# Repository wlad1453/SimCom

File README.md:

# SimCom
This project realizes an ultrasonic distance measurement and determines a presence time of a truck in the measurement field. These data are send to the server via GPRS/HTTP technology. On the server side this data are analized and an intermediate data file (sim800truck_data.txt) as well as an DB entry are created or updated.
The visualization of the actual data is done via WEB interface (sim800data.php). 
With the help of a JS scripts and AJAX method the data file sim800truck_data.txt and the last db entry is read every 500 mS and the actual data are
presented via WEB-inteface.

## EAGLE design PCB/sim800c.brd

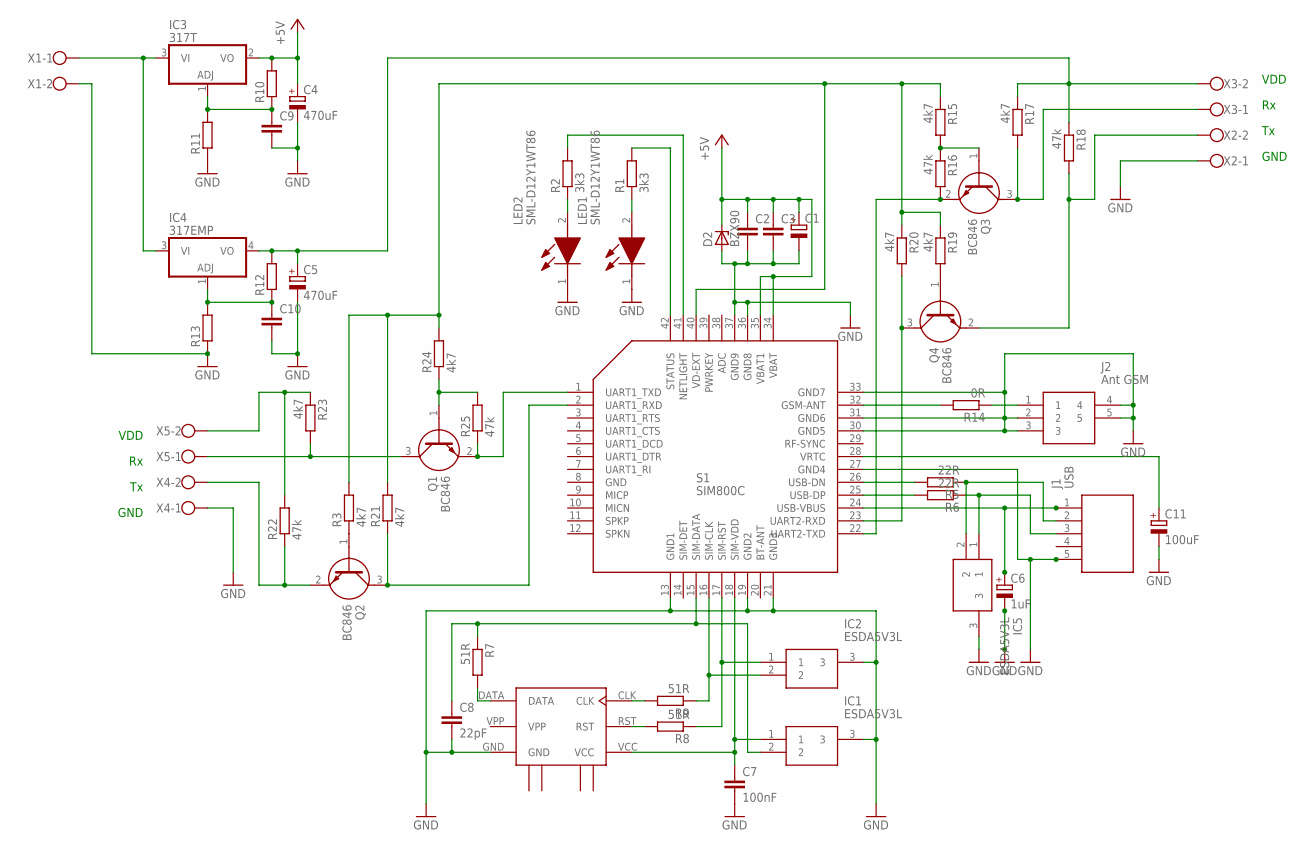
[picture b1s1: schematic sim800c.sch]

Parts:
C1: CPOL-EU140CLH-0810; 140CLH-0810
C2, C3, C9, C10: C-EUC0603; C0603
C4, C5: 470uF; 140CLH-1010
C6: 1uF; 153CLV-0405
C7: 100nF; C0805
C8: 22pF; C0805
C11: 100uF; 140CLH-0810
D2: BZX90; DO34Z7
IC1: ESDA5V3L; SOT105P242X150-3N
IC2, IC5: ESDA5V3L; SOT105P242X150-3N; MANUFACTURER_PART_NUMBER ESDA5V3L; MOUSER_PART_NUMBER 511-ESDA5V3L
IC3: 317T; TO220H
IC4: 317EMP; SOT223
J1: USB; ZX62R-B-5P(30)
J2: Ant GSM; 10533541
LED1, LED2: SML-D12Y1WT86; LEDC1608X55N
Q1, Q2: BC846; SOT95P230X110-3N
Q3, Q4: BC846; SOT95P230X110-3N; MANUFACTURER_PART_NUMBER BC846B,215; MOUSER_PART_NUMBER 771-BC846B-T/R
R1, R2: 3k3; M0805
R3, R15, R17, R19, R20, R21, R23, R24: 4k7; M1206
R5, R6: 22R; M1206
R7, R8, R9: 51R; M1206
R10, R11, R12, R13: R-EU_M1206; M1206
R14: 0R; M1206
R16, R18, R22, R25: 47k; M1206
S1: SIM800C
U$1: SCU-W0822XR-06
X1, X2, X4: W237-102
X3, X5: W237-102; MPN 237-102

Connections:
+5V: C1.+, C2.1, C3.1, C4.+, D2.C, IC3.2 (VO), R10.2, S1.34 (VBAT), S1.35 (VBAT1)
GND: C1.-, C2.2, C3.2, C4.-, C5.-, C6.-, C7.2, C8.2, C9.2, C10.2, C11.-, D2.A, IC1.3, IC2.3, IC5.3, J1.5, J2.2, J2.3, J2.4, J2.5, LED1.1 (K), LED2.1 (K), R11.1, R13.1, S1.8 (GND), S1.13 (GND1), S1.19 (GND2), S1.21 (GND3), S1.27 (GND4), S1.30 (GND5), S1.31 (GND6), S1.33 (GND7), S1.36 (GND8), S1.37 (GND9), U$1.GND, X1.2, X2.1, X4.1
GND1: U$1.GND_1 (GND1)
GND2: U$1.GND_2 (GND2)
GND3: U$1.GND_3 (GND3)
GND4: U$1.GND_4 (GND4)
unnamed: Q3.2 (E), R16.2, S1.22 (UART2-TXD)
unnamed: R6.2, S1.25 (USB-DP)
unnamed: C6.+, J1.1, S1.24 (USB-VBUS)
unnamed: IC5.2, J1.2, R5.1
unnamed: R14.2, S1.32 (GSM-ANT)
unnamed: LED1.2 (A), R1.1
unnamed: LED2.2 (A), R2.1
unnamed: Q1.3 (C), R23.2, X5.1
unnamed: Q1.1 (B), R24.1, R25.2
unnamed: IC5.1, J1.3, R6.1
unnamed: Q2.3 (C), R21.1, S1.2 (UART1_RXD)
unnamed: R7.2, U$1.DATA
unnamed: IC2.2, R9.1, S1.16 (SIM-CLK)
unnamed: IC2.1, R8.1, S1.17 (SIM-RST)
unnamed: IC3.3 (VI), IC4.3 (VI), X1.1
unnamed: C7.1, IC1.1, S1.18 (SIM-VDD), U$1.VCC
unnamed: C8.1, IC1.2, R7.1, S1.15 (SIM-DATA)
unnamed: C9.1, IC3.1 (ADJ), R10.1, R11.2
unnamed: R9.2, U$1.CLK
unnamed: J2.1, R14.1
unnamed: R8.2, U$1.RST
unnamed: R2.2, S1.41 (NETLIGHT)
unnamed: R1.2, S1.42 (STATUS)
unnamed: C10.1, IC4.1 (ADJ), R12.1, R13.2
unnamed: C11.+, S1.28 (VRTC)
unnamed: Q3.1 (B), R15.2, R16.1
unnamed: C5.+, IC4.4 (VO), R12.2, R17.1, R18.1, X3.2
unnamed: R5.2, S1.26 (USB-DN)
unnamed: R3.2, R15.1, R19.1, R20.1, R21.2, R24.2, S1.40 (VD-EXT)
unnamed: Q2.2 (E), R22.1, X4.2
unnamed: Q3.3 (C), R17.2, X3.1
unnamed: Q2.1 (B), R3.1
unnamed: Q4.1 (B), R19.2
unnamed: Q4.3 (C), R20.2, S1.23 (UART2-RXD)
unnamed: Q4.2 (E), R18.2, X2.2
unnamed: R22.2, R23.1, X5.2
S$3: Q1.2 (E), R25.1, S1.1 (UART1_TXD)
VPP: U$1.VPP

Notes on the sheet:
VDD
GND

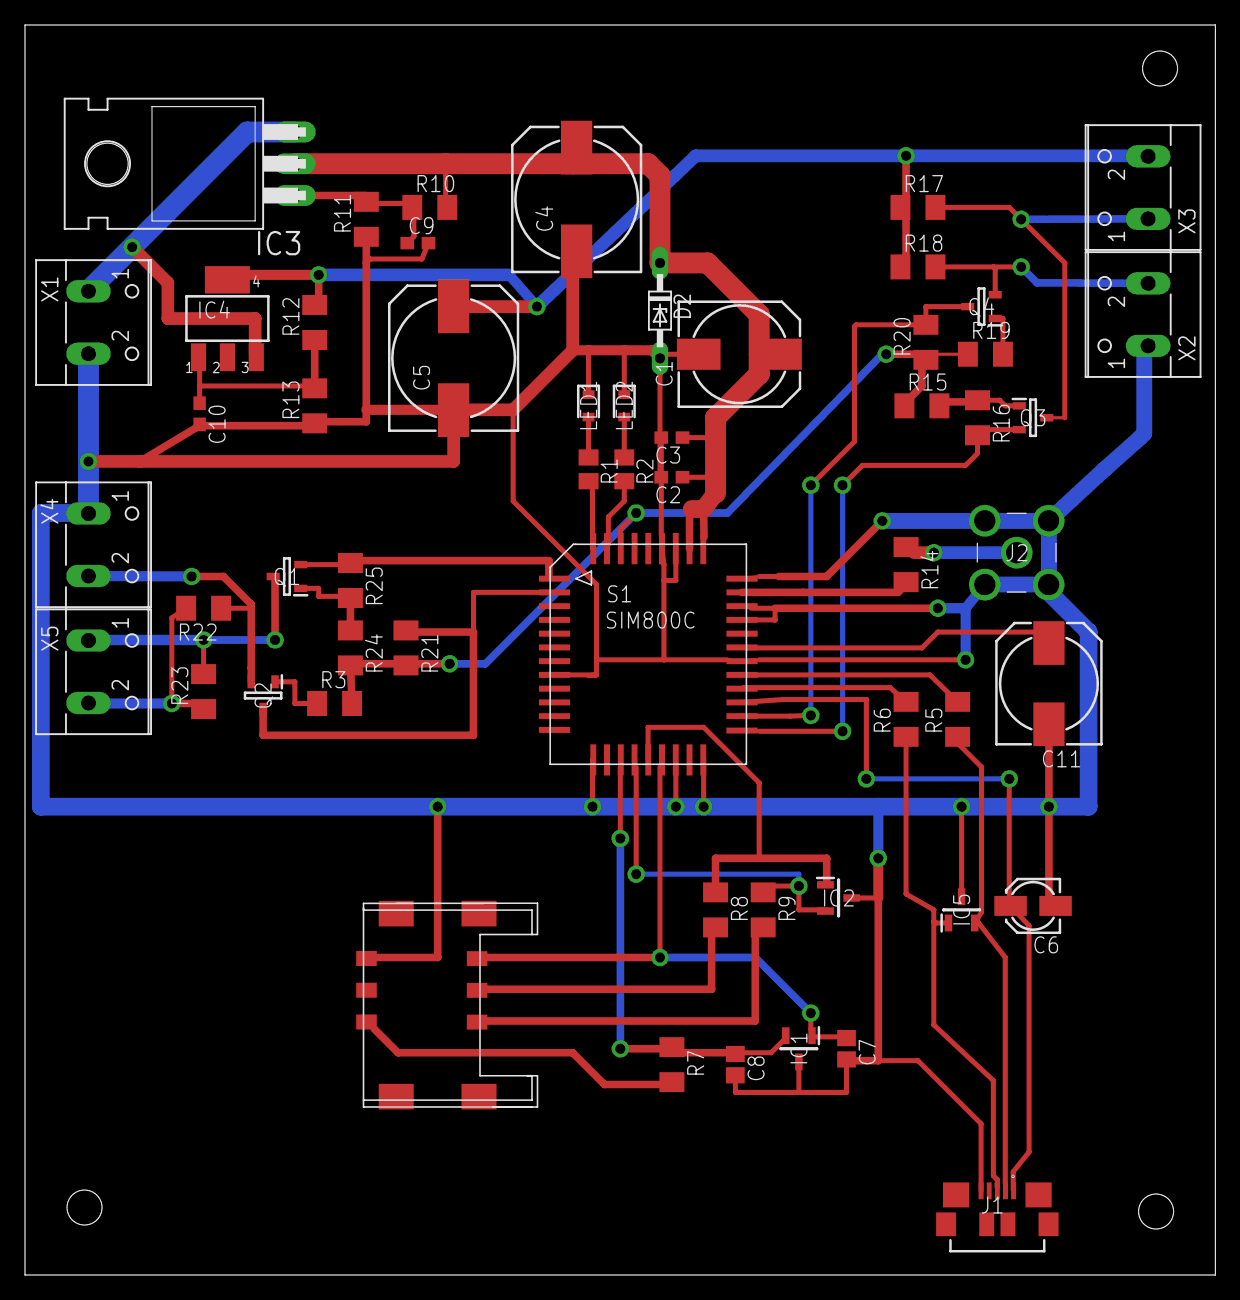
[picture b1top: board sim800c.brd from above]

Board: 2 copper layers, 95.2 x 100.0 mm, 56 parts (0 on the bottom side), 39 nets.

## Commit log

2020-10-08 Add files via upload
    AT commands structures added,
    send/recieve logic implementation started
2020-10-08 Add files via upload
    These files implement a server side functionality
2020-10-08 Rename answ_time.php to WEB interface/answ_time.php
2020-10-08 Rename host_time.php to WEB interface/host_time.php
2020-10-08 Rename sim800connect.php to WEB interface/sim800connect.php
2020-10-08 Rename sim800data.php to WEB interface/sim800data.php
2020-10-08 Rename sim800truck_data.txt to WEB interface/sim800truck_data.txt
2020-10-08 Rename trucks_data.txt to WEB interface/trucks_data.txt
2020-10-08 Rename sim800_README.md to README.md
